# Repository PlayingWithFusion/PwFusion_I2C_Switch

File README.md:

# PwFusion_I2C_Switch

Are you looking for a way to take your project to the next level? Playing with Fusion's I2C Switch board is the way to go! This device greatly simplifies connectivity to a microcontroller through the QWIIC system. The typical 2 wires required to a toggle switch with a microcontroller can be reduced to one QWIIC cable. You can even chain multiple QWIIC devices together for maximum wiring efficiency! If that isn't enough, Playing with Fusion provides Arduino libraries to make writing code for these boards as easy as possible! Weather you are a beginner looking for a simple introduction to the world of hobbyist electronics or an advanced user looking for a rapid prototyping tool, Playing with Fusion's I2C Switch is right for you!

## I2C Addresses

| ADR   |   Address |
| --- | --- |
| uncut |   0x13  |
| cut   |   0x14  |

Each Playing with Fusion I2C switch board comes with 2 available I2C addresses, which can be easily selected by disconnecting a jumper on the printed circuit board. This allows for 2 toggle switch boards to be used on the same QWIIC chain. If you would like more than 2, see docs/Programming Instructions and flash a modified firmware with additional I2C address options.

## Example Projects
RC Transmitter: https://github.com/PlayingWithFusion/RC_Transmitter

## Related
| Page | Link |
| --- | --- |
| PwFusion_I2C_Toggle_Arduino_Library: |   https://github.com/PlayingWithFusion/PwFusion_I2C_Toggle_Arduino_Library |
| PwFusion_Data_Transfer:              |   https://github.com/PlayingWithFusion/PwFusion_Data_Transfer |
| IFB-40001 PwFusion_I2C_Encoder: |    https://github.com/PlayingWithFusion/PwFusion_I2C_Encoder |
| IFB-40002 PwFusion_I2C_Joystick:  |  https://github.com/PlayingWithFusion/PwFusion_I2C_Joystick |
| IFB-40003 PwFusion_I2C_Switch:   |   https://github.com/PlayingWithFusion/PwFusion_I2C_Switch |
| IFB-40004 PwFusion_I2C_Buttons:  |   https://github.com/PlayingWithFusion/PwFusion_I2C_Buttons |

Visit https://www.playingwithfusion.com/ for more information.

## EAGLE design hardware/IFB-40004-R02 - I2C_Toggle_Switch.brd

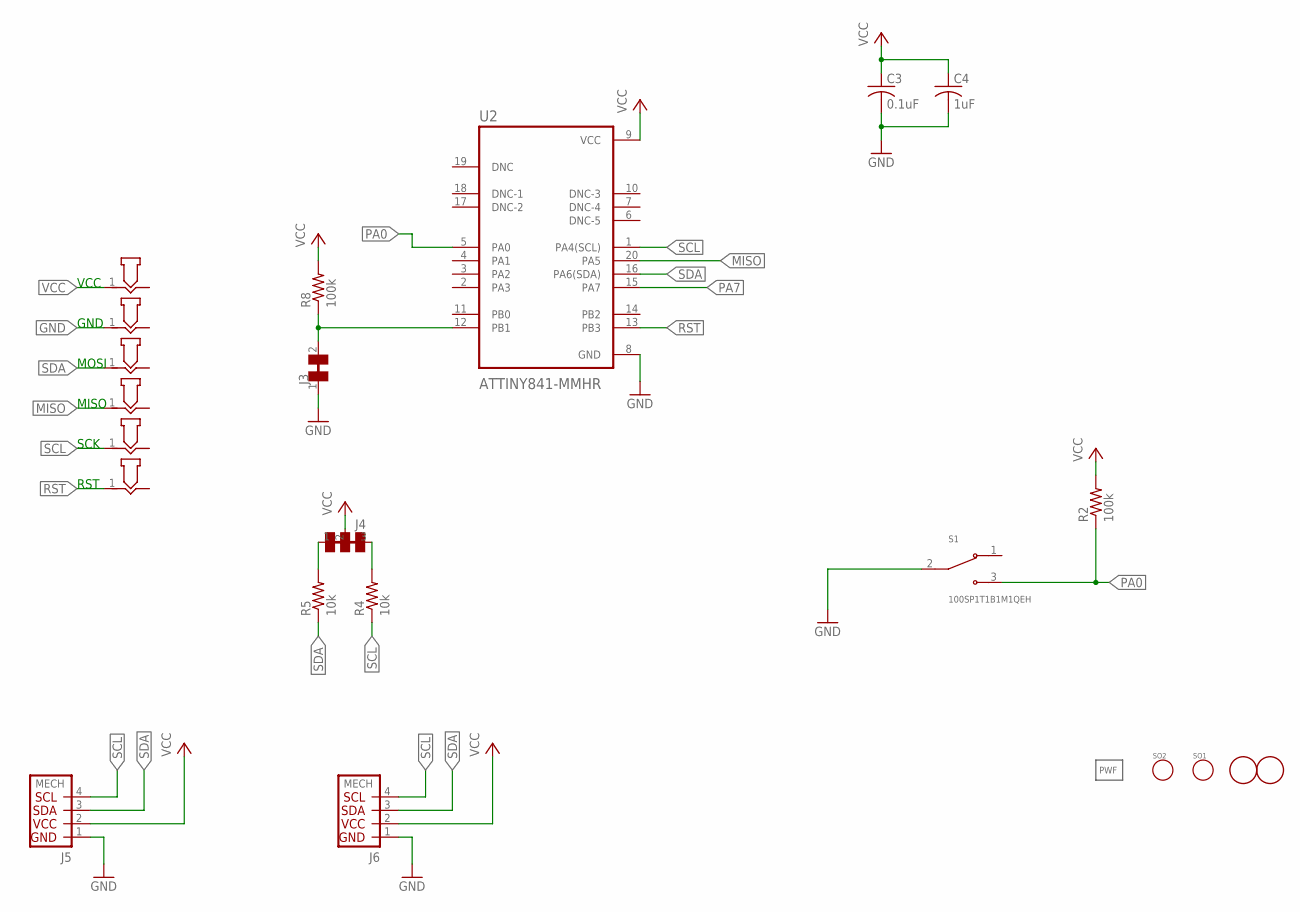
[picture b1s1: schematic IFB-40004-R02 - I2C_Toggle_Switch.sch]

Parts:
C3: 0.1uF; C0603K
C4: 1uF; C0603K
GND: POGO_PAD; P50_POGO_BOARD_CONTACT_12MIL
J3: CUTTABLE_JUMPER; SMT_CUTTABLE_JUMPER
J4: CUT_JUMPER_2X; SMT_2X_CUTTABLE_JUMPER
J5, J6: QWIICSIDE; SM04B-SRSS-TB
LOGO1: PWF_LOGOPWF-5MM-SS; LOGO_5MM_STEIN
MISO: POGO_PAD; P50_POGO_BOARD_CONTACT_12MIL
MOSI: POGO_PAD; P50_POGO_BOARD_CONTACT_12MIL
R2, R8: 100k; R0603
R4, R5: 10k; R0603
RST: POGO_PAD; P50_POGO_BOARD_CONTACT_12MIL
S1: 100SP1T1B1M1QEH; SW_100SP1T1B1M1QEH
SCK: POGO_PAD; P50_POGO_BOARD_CONTACT_12MIL
SO1, SO2: STAND_OFFNO4_TIGHT; STANDOFF_NO4_TIGHT
U2: ATTINY841-MMHR; QFN45P300X300X85-21N
U$2, U$3: FIDUCIAL; FIDUCIAL_1MM
VCC: POGO_PAD; P50_POGO_BOARD_CONTACT_12MIL

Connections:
GND: C3.2, C4.2, GND.1, J3.1, J5.1, J6.1, S1.2, U2.8 (GND)
MISO: MISO.1, U2.20 (PA5)
unnamed: J3.2, R8.1, U2.12 (PB1)
unnamed: J4.1, R5.2
unnamed: J4.3, R4.2
PA0: R2.1, S1.3, U2.5 (PA0)
PA7: U2.15 (PA7)
RST: RST.1, U2.13 (PB3)
SCL: J5.4, J6.4, R4.1, SCK.1, U2.1 (PA4(SCL))
SDA: J5.3, J6.3, MOSI.1, R5.1, U2.16 (PA6(SDA))
VCC: C3.1, C4.1, J4.2, J5.2, J6.2, R2.2, R8.2, U2.9 (VCC), VCC.1

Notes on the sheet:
VCC
GND
MOSI
MISO
SCK
RST

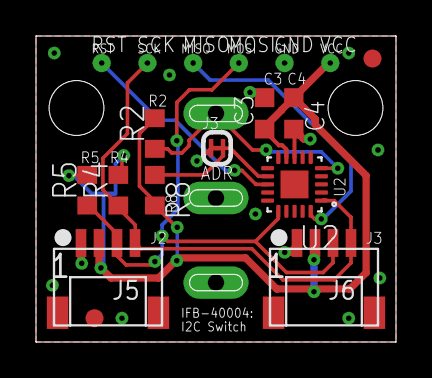
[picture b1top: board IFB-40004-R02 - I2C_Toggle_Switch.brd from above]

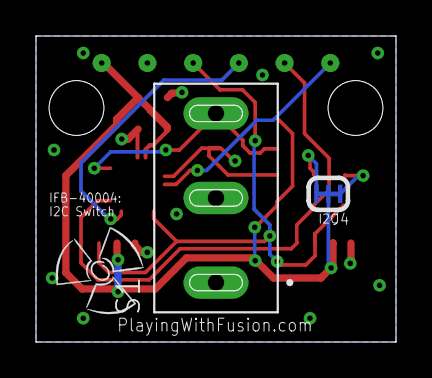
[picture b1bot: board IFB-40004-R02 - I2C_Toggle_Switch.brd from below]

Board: 2 copper layers, 20.0 x 17.0 mm, 23 parts (3 on the bottom side), 10 nets.

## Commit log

2023-10-01 Added firmware and readme
2023-10-08 hardware and links
2023-10-29 added programming instructions
2023-12-02 updated addresses
2023-12-02 updated hardware files
2024-07-05 updated firmware flash instructions
